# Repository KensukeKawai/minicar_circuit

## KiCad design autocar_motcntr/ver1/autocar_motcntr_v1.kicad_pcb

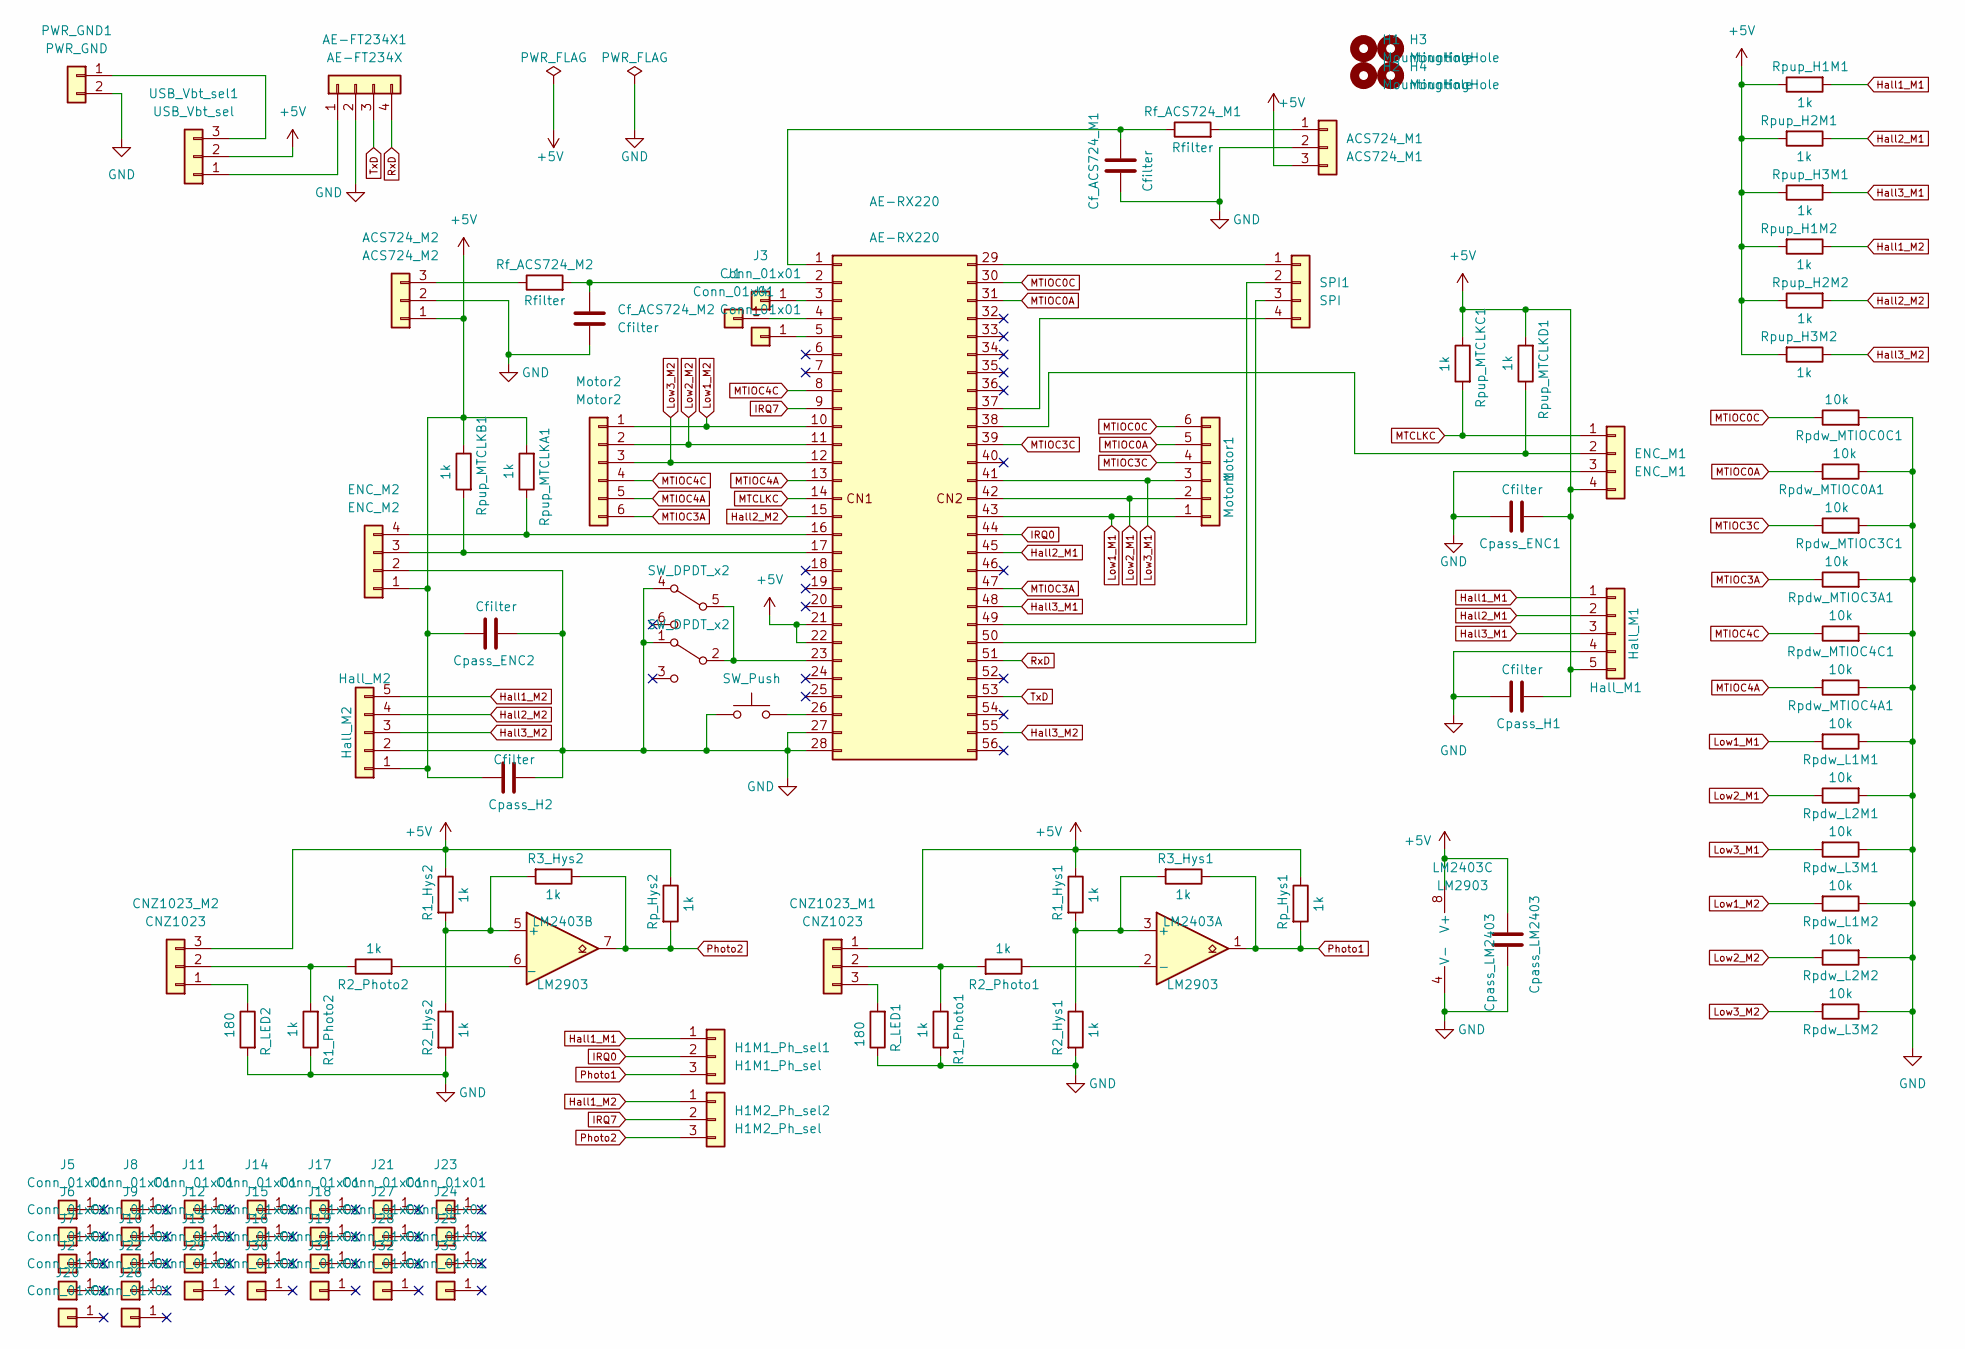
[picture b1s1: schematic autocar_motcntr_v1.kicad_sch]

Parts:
ACS724_M1: ACS724_M1; JST_XH_B3B-XH-A_1x03_P2.50mm_Vertical
ACS724_M2: ACS724_M2; JST_XH_B3B-XH-A_1x03_P2.50mm_Vertical
AE-FT234X1: AE-FT234X
AE-RX220: AE-RX220
CNZ1023_M1, CNZ1023_M2: CNZ1023; JST_XH_B3B-XH-A_1x03_P2.50mm_Vertical
Cf_ACS724_M1, Cf_ACS724_M2: Cfilter; C_Disc_D3.0mm_W2.0mm_P2.50mm
Cpass_ENC1, Cpass_ENC2: Cfilter; C_Disc_D3.0mm_W2.0mm_P2.50mm
Cpass_H1, Cpass_H2: Cfilter; C_Disc_D3.0mm_W2.0mm_P2.50mm
Cpass_LM2403: Cpass_LM2403; C_Disc_D3.0mm_W2.0mm_P2.50mm
ENC_M1: ENC_M1; JST_XH_B4B-XH-A_1x04_P2.50mm_Vertical
ENC_M2: ENC_M2; JST_XH_B4B-XH-A_1x04_P2.50mm_Vertical
H1, H2, H3, H4: MountingHole; MountingHole_3.2mm_M3
H1M1_Ph_sel1: H1M1_Ph_sel; PinHeader_1x03_P2.54mm_Vertical
H1M2_Ph_sel2: H1M2_Ph_sel; PinHeader_1x03_P2.54mm_Vertical
Hall_M1: Hall_M1; JST_XH_B5B-XH-A_1x05_P2.50mm_Vertical
Hall_M2: Hall_M2; JST_XH_B5B-XH-A_1x05_P2.50mm_Vertical
J1, J2, J3, J4, J5, J6, J7, J8, J9, J10, J11, J12, J13, J14, J15, J16, J17, J18, J19, J20, J21, J22, J23, J24, J25, J26, J27, J28, J29, J30, J31, J32, J33: Conn_01x01; TestPoint_THTPad_D1.5mm_Drill0.7mm
LM2403: LM2903; DIP-8_W7.62mm
Motor1: Motor1; JST_XH_B6B-XH-A_1x06_P2.50mm_Vertical
Motor2: Motor2; JST_XH_B6B-XH-A_1x06_P2.50mm_Vertical
PWR_GND1: PWR_GND; TB-111-2
R1_Hys1, R1_Hys2, R1_Photo1, R1_Photo2, R2_Hys1, R2_Hys2, R2_Photo1, R2_Photo2: 1k; R_Axial_DIN0207_L6.3mm_D2.5mm_P2.54mm_Vertical
R3_Hys1, R3_Hys2: 1k; R_Axial_DIN0207_L6.3mm_D2.5mm_P7.62mm_Horizontal
R_LED1, R_LED2: 180; R_Axial_DIN0207_L6.3mm_D2.5mm_P2.54mm_Vertical
Rf_ACS724_M1, Rf_ACS724_M2: Rfilter; R_Axial_DIN0207_L6.3mm_D2.5mm_P2.54mm_Vertical
Rp_Hys1, Rp_Hys2: 1k; R_Axial_DIN0207_L6.3mm_D2.5mm_P2.54mm_Vertical
Rpdw_L1M1, Rpdw_L1M2, Rpdw_L2M1, Rpdw_L2M2, Rpdw_L3M1, Rpdw_L3M2: 10k; R_Axial_DIN0207_L6.3mm_D2.5mm_P2.54mm_Vertical
Rpdw_MTIOC0A1, Rpdw_MTIOC0C1, Rpdw_MTIOC3A1, Rpdw_MTIOC3C1, Rpdw_MTIOC4A1, Rpdw_MTIOC4C1: 10k; R_Axial_DIN0207_L6.3mm_D2.5mm_P2.54mm_Vertical
Rpup_H1M1, Rpup_H1M2, Rpup_H2M1, Rpup_H2M2, Rpup_H3M1, Rpup_H3M2: 1k; R_Axial_DIN0207_L6.3mm_D2.5mm_P2.54mm_Vertical
Rpup_MTCLKA1: 1k; R_Axial_DIN0207_L6.3mm_D2.5mm_P2.54mm_Vertical
Rpup_MTCLKB1: 1k; R_Axial_DIN0207_L6.3mm_D2.5mm_P2.54mm_Vertical
Rpup_MTCLKC1: 1k; R_Axial_DIN0207_L6.3mm_D2.5mm_P2.54mm_Vertical
Rpup_MTCLKD1: 1k; R_Axial_DIN0207_L6.3mm_D2.5mm_P2.54mm_Vertical
SPI1: SPI; JST_XH_B4B-XH-A_1x04_P2.50mm_Vertical
SW1: SW_DPDT_x2; SW_E-Switch_EG1271_DPDT
SW2: SW_Push; SW_Tactile_Straight_KSA0Axx1LFTR
USB_Vbt_sel1: USB_Vbt_sel; PinHeader_1x03_P2.54mm_Vertical

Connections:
+5V: ACS724_M1.3, ACS724_M2.1, AE-RX220.21 (CN1-21), AE-RX220.22 (CN1-22), CNZ1023_M1.1, CNZ1023_M2.3, Cpass_ENC1.2, Cpass_ENC2.1, Cpass_H1.2, Cpass_H2.1, Cpass_LM2403.2, ENC_M1.4, ENC_M2.1, Hall_M1.5, Hall_M2.1, LM2403.8 (V+), R1_Hys1.1, R1_Hys2.1, Rp_Hys1.1, Rp_Hys2.1, Rpup_H1M1.1, Rpup_H1M2.2, Rpup_H2M1.2, Rpup_H2M2.1, Rpup_H3M1.1, Rpup_H3M2.2, Rpup_MTCLKA1.2, Rpup_MTCLKB1.1, Rpup_MTCLKC1.1, Rpup_MTCLKD1.2, USB_Vbt_sel1.2
GND: ACS724_M1.2, ACS724_M2.2, AE-FT234X1.2 (GND), AE-RX220.27 (CN1-27), AE-RX220.28 (CN1-28), Cf_ACS724_M1.2, Cf_ACS724_M2.2, Cpass_ENC1.1, Cpass_ENC2.2, Cpass_H1.1, Cpass_H2.2, Cpass_LM2403.1, ENC_M1.3, ENC_M2.2, Hall_M1.4, Hall_M2.2, LM2403.4 (V-), PWR_GND1.2, R1_Photo1.2, R1_Photo2.1, R2_Hys1.2, R2_Hys2.2, R_LED1.1, R_LED2.2, Rpdw_L1M1.1, Rpdw_L1M2.1, Rpdw_L2M1.2, Rpdw_L2M2.2, Rpdw_L3M1.1, Rpdw_L3M2.1, Rpdw_MTIOC0A1.1, Rpdw_MTIOC0C1.2, Rpdw_MTIOC3A1.2, Rpdw_MTIOC3C1.2, Rpdw_MTIOC4A1.1, Rpdw_MTIOC4C1.2, SW1.1 (A), SW1.4 (A), SW2.2
Hall1_M1: H1M1_Ph_sel1.1, Hall_M1.1, Rpup_H1M1.2
Hall1_M2: H1M2_Ph_sel2.1, Hall_M2.5, Rpup_H1M2.1
Hall2_M1: AE-RX220.45 (CN2-17), Hall_M1.2, Rpup_H2M1.1
Hall2_M2: AE-RX220.15 (CN1-15), Hall_M2.4, Rpup_H2M2.2
Hall3_M1: AE-RX220.48 (CN2-20), Hall_M1.3, Rpup_H3M1.2
Hall3_M2: AE-RX220.55 (CN2-27), Hall_M2.3, Rpup_H3M2.1
IRQ0: AE-RX220.44 (CN2-16), H1M1_Ph_sel1.2
IRQ7: AE-RX220.9 (CN1-09), H1M2_Ph_sel2.2
Low1_M1: AE-RX220.43 (CN2-15), Motor1.1, Rpdw_L1M1.2
Low1_M2: AE-RX220.10 (CN1-10), Motor2.1, Rpdw_L1M2.2
Low2_M1: AE-RX220.42 (CN2-14), Motor1.2, Rpdw_L2M1.1
Low2_M2: AE-RX220.11 (CN1-11), Motor2.2, Rpdw_L2M2.1
Low3_M1: AE-RX220.41 (CN2-13), Motor1.3, Rpdw_L3M1.2
Low3_M2: AE-RX220.12 (CN1-12), Motor2.3, Rpdw_L3M2.2
MTCLKC: AE-RX220.14 (CN1-14), ENC_M1.1, Rpup_MTCLKC1.2
MTIOC0A: AE-RX220.31 (CN2-03), Motor1.5, Rpdw_MTIOC0A1.2
MTIOC0C: AE-RX220.30 (CN2-02), Motor1.6, Rpdw_MTIOC0C1.1
MTIOC3A: AE-RX220.47 (CN2-19), Motor2.6, Rpdw_MTIOC3A1.1
MTIOC3C: AE-RX220.39 (CN2-11), Motor1.4, Rpdw_MTIOC3C1.1
MTIOC4A: AE-RX220.13 (CN1-13), Motor2.5, Rpdw_MTIOC4A1.2
MTIOC4C: AE-RX220.8 (CN1-08), Motor2.4, Rpdw_MTIOC4C1.1
unnamed: ACS724_M1.1, Rf_ACS724_M1.2
unnamed: ACS724_M2.3, Rf_ACS724_M2.1
unnamed: AE-FT234X1.1 (5V(VUSB)), USB_Vbt_sel1.1
unnamed: AE-RX220.1 (CN1-01), Cf_ACS724_M1.1, Rf_ACS724_M1.1
unnamed: AE-RX220.2 (CN1-02), Cf_ACS724_M2.1, Rf_ACS724_M2.2
unnamed: AE-RX220.3 (CN1-03), J3.1
unnamed: AE-RX220.4 (CN1-04), J1.1
unnamed: AE-RX220.5 (CN1-05), J4.1
unnamed: AE-RX220.16 (CN1-16), ENC_M2.4, Rpup_MTCLKA1.1
unnamed: AE-RX220.17 (CN1-17), ENC_M2.3, Rpup_MTCLKB1.2
unnamed: AE-RX220.23 (CN1-23), SW1.2 (B), SW1.5 (B)
unnamed: AE-RX220.26 (CN1-26), SW2.1
unnamed: AE-RX220.29 (CN2-01), SPI1.1
unnamed: AE-RX220.37 (CN2-09), SPI1.4
unnamed: AE-RX220.38 (CN2-10), ENC_M1.2, Rpup_MTCLKD1.1
unnamed: AE-RX220.49 (CN2-21), SPI1.2
unnamed: AE-RX220.50 (CN2-22), SPI1.3
unnamed: CNZ1023_M1.2, R1_Photo1.1, R2_Photo1.2
unnamed: CNZ1023_M1.3, R_LED1.2
unnamed: CNZ1023_M2.1, R_LED2.1
unnamed: CNZ1023_M2.2, R1_Photo2.2, R2_Photo2.1
unnamed: LM2403.2 (-), R2_Photo1.1
unnamed: LM2403.3 (+), R1_Hys1.2, R2_Hys1.1, R3_Hys1.2
unnamed: LM2403.5 (+), R1_Hys2.2, R2_Hys2.1, R3_Hys2.2
unnamed: LM2403.6 (_), R2_Photo2.2
unnamed: PWR_GND1.1, USB_Vbt_sel1.3
Photo1: H1M1_Ph_sel1.3, LM2403.1, R3_Hys1.1, Rp_Hys1.2
Photo2: H1M2_Ph_sel2.3, LM2403.7, R3_Hys2.1, Rp_Hys2.2
RxD: AE-FT234X1.4 (RxD), AE-RX220.51 (CN2-23)
TxD: AE-FT234X1.3 (TxD), AE-RX220.53 (CN2-25)

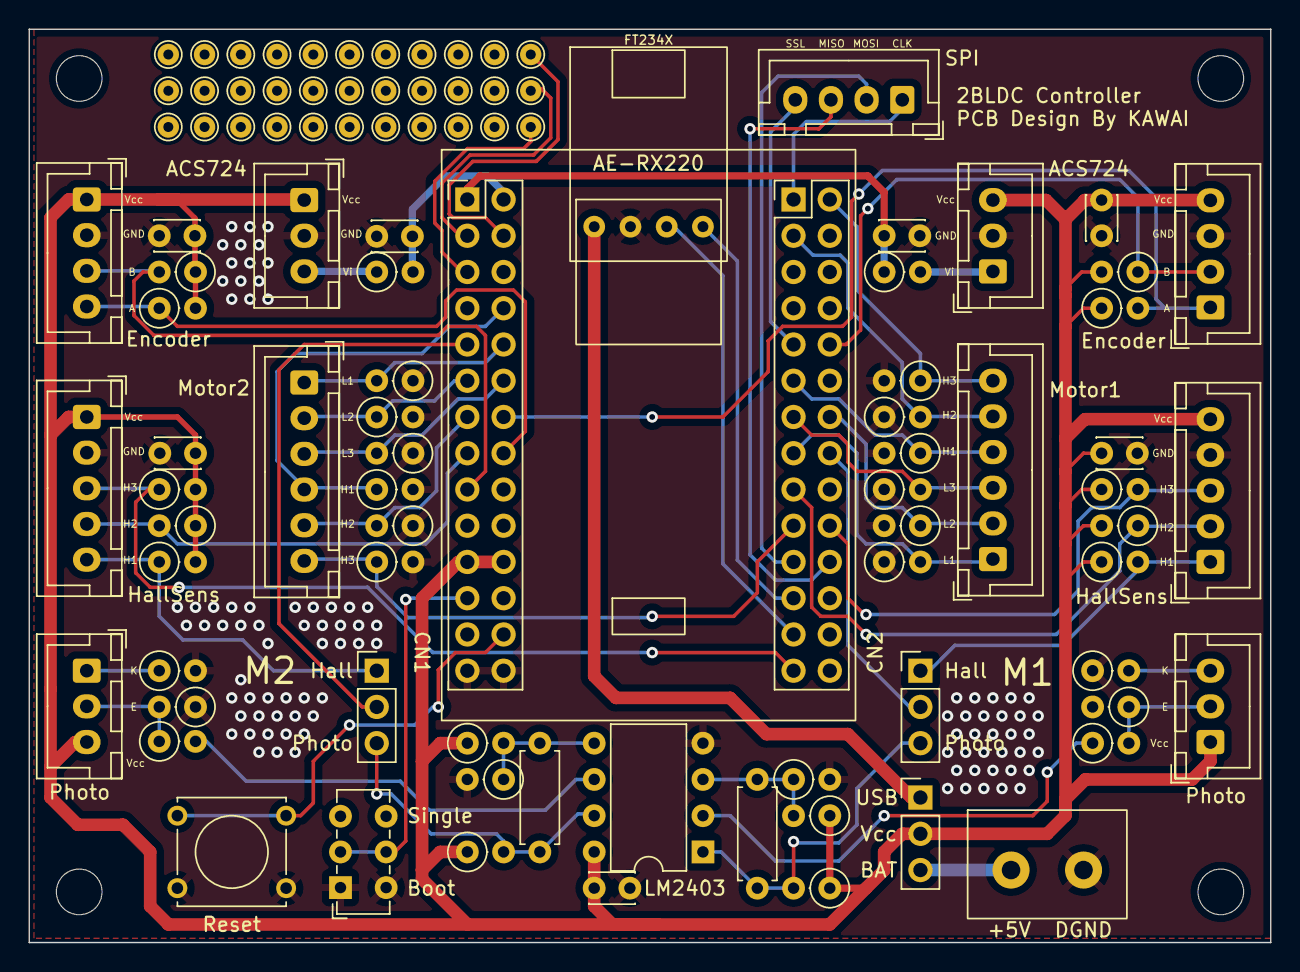
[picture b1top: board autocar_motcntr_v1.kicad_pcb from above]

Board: 2 copper layers, 87.0 x 64.0 mm, 102 parts (0 on the bottom side), 53 nets.

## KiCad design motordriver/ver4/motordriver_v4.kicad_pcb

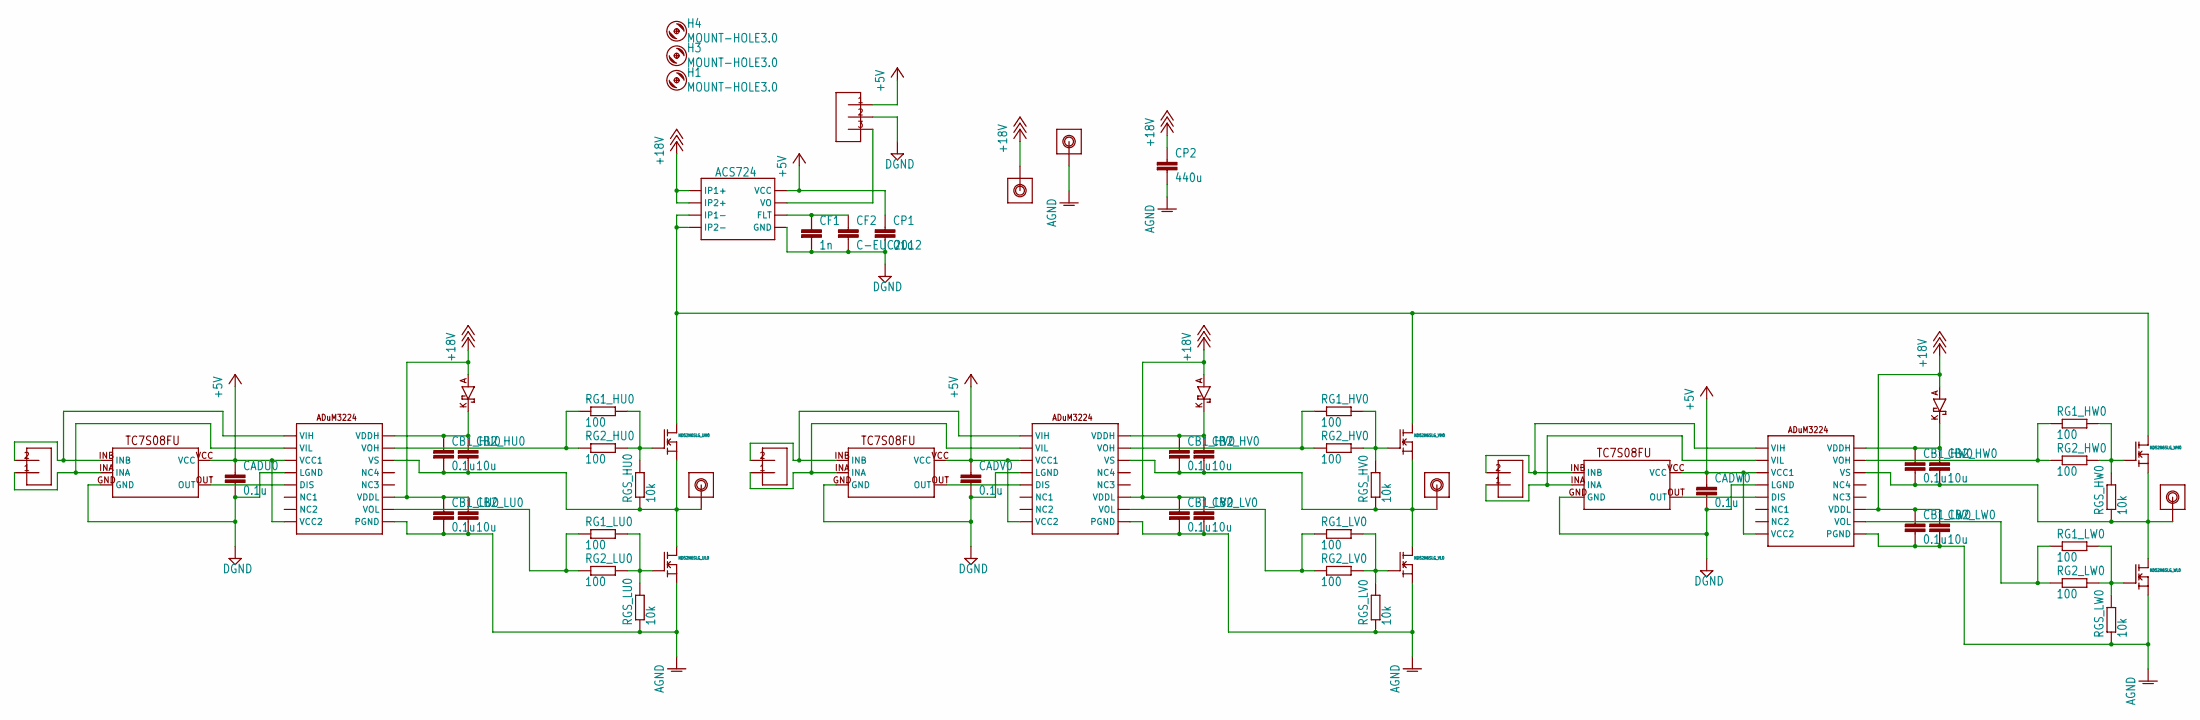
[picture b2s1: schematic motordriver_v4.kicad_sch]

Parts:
ACS724: ACS724
ADUM3224_U0, ADUM3224_V0: ADUM3224; SO16
CADU0: 0.1u; C2012
CADV0: 0.1u; C2012
CADW0: 0.1u; C2012
CB1_HU0, CB1_HV0, CB1_HW0, CB1_LU0, CB1_LV0, CB1_LW0: 0.1u; C2012
CB2_HU0, CB2_HV0, CB2_HW0, CB2_LU0, CB2_LV0, CB2_LW0: 10u; C3225
CF1: 1n; C1608
CF2: C-EUC2012; C2012
CP1: 01u; C2012
CP2: 440u; CP_Radial_D10.0mm_P5.00mm
H1, H3, H4: MOUNT-HOLE3.0; 3,0
ND52N6SLG_UH0, ND52N6SLG_UL0, ND52N6SLG_VH0, ND52N6SLG_VL0, ND52N6SLG_WH0, ND52N6SLG_WL0: ND52N6SLG; TO252
RG1_HU0, RG1_HV0, RG1_HW0, RG1_LU0, RG1_LV0, RG1_LW0, RG2_HU0, RG2_HV0, RG2_HW0, RG2_LU0, RG2_LV0, RG2_LW0: 100; R3216
RGS_HU0: 10k; R3216
RGS_HV0: 10k; R3216
RGS_HW0: 10k; R3216
RGS_LU0: 10k; R3216
RGS_LV0: 10k; R3216
RGS_LW0: 10k; R3216
SBD_U0: SBR1U200P1
SBD_V0: SBR1U200P1
U$1, U$7, U$14, U$15, U$16: PV-3
U$2, U$9, U$13: B2B-XH-A
U$4: B3B-XH-A
U$5, U$8, U$12: TC7S08FU
U$10: ADUM3224; SO16
U$11: SBR1U200P1

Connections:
+5V: ACS724.VCC, ADUM3224_U0.VCC1, ADUM3224_U0.VCC2, ADUM3224_V0.VCC1, ADUM3224_V0.VCC2, CADU0.1, CADV0.1, CADW0.1, CP1.1, U$4.1, U$5.VCC, U$8.VCC, U$10.VCC1, U$10.VCC2, U$12.VCC
AGND: ADUM3224_U0.PGND, ADUM3224_V0.PGND, CB1_LU0.2, CB1_LV0.2, CB1_LW0.2, CB2_LU0.2, CB2_LV0.2, CB2_LW0.2, CP2.2, ND52N6SLG_UL0.3 (S), ND52N6SLG_VL0.3 (S), ND52N6SLG_WL0.3 (S), RGS_LU0.1, RGS_LV0.1, RGS_LW0.1, U$7.P$1, U$10.PGND; also elsewhere on the board
DGND: ACS724.GND, ADUM3224_U0.LGND, ADUM3224_V0.LGND, CADU0.2, CADV0.2, CADW0.2, CF1.2, CF2.2, CP1.2, U$4.2, U$5.GND, U$8.GND, U$10.LGND, U$12.GND
unnamed: ACS724.IP1-, ACS724.IP2-, ND52N6SLG_UH0.4 (D), ND52N6SLG_VH0.4 (D), ND52N6SLG_WH0.4 (D)
unnamed: ACS724.FLT, CF1.1, CF2.1
unnamed: ADUM3224_U0.VOH, RG1_HU0.1, RG2_HU0.1
unnamed: ADUM3224_U0.DIS, U$5.OUT
unnamed: ND52N6SLG_UL0.1 (G), RG1_LU0.2, RG2_LU0.2, RGS_LU0.2
unnamed: ADUM3224_U0.VIH, U$2.2, U$5.INB
unnamed: ND52N6SLG_UH0.1 (G), RG1_HU0.2, RG2_HU0.2, RGS_HU0.2
unnamed: ADUM3224_U0.VOL, RG1_LU0.1, RG2_LU0.1
unnamed: ND52N6SLG_VL0.1 (G), RG1_LV0.2, RG2_LV0.2, RGS_LV0.2
unnamed: ADUM3224_U0.VDDH, CB1_HU0.1, CB2_HU0.1, SBD_U0.K
unnamed: ADUM3224_U0.VS, CB1_HU0.2, CB2_HU0.2, ND52N6SLG_UH0.3 (S), ND52N6SLG_UL0.4 (D), RGS_HU0.1, U$14.P$1
unnamed: ADUM3224_U0.VIL, U$2.1, U$5.INA
unnamed: ND52N6SLG_VH0.1 (G), RG1_HV0.2, RG2_HV0.2, RGS_HV0.2
unnamed: ADUM3224_V0.VDDH, CB1_HV0.1, CB2_HV0.1, SBD_V0.K
unnamed: ADUM3224_V0.VS, CB1_HV0.2, CB2_HV0.2, ND52N6SLG_VH0.3 (S), ND52N6SLG_VL0.4 (D), RGS_HV0.1, U$15.P$1
unnamed: ADUM3224_V0.VOH, RG1_HV0.1, RG2_HV0.1
unnamed: ADUM3224_V0.VOL, RG1_LV0.1, RG2_LV0.1
unnamed: ADUM3224_V0.DIS, U$8.OUT
unnamed: ADUM3224_V0.VIH, U$8.INB, U$9.2
unnamed: ADUM3224_V0.VIL, U$8.INA, U$9.1
unnamed: ACS724.VO, U$4.3
unnamed: ND52N6SLG_WL0.1 (G), RG1_LW0.2, RG2_LW0.2, RGS_LW0.2
unnamed: ND52N6SLG_WH0.1 (G), RG1_HW0.2, RG2_HW0.2, RGS_HW0.2
unnamed: CB1_HW0.1, CB2_HW0.1, U$10.VDDH, U$11.K
unnamed: CB1_HW0.2, CB2_HW0.2, ND52N6SLG_WH0.3 (S), ND52N6SLG_WL0.4 (D), RGS_HW0.1, U$10.VS, U$16.P$1
unnamed: RG1_HW0.1, RG2_HW0.1, U$10.VOH
unnamed: RG1_LW0.1, RG2_LW0.1, U$10.VOL
unnamed: U$10.DIS, U$12.OUT
unnamed: U$10.VIH, U$12.INB, U$13.2
unnamed: U$10.VIL, U$12.INA, U$13.1

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
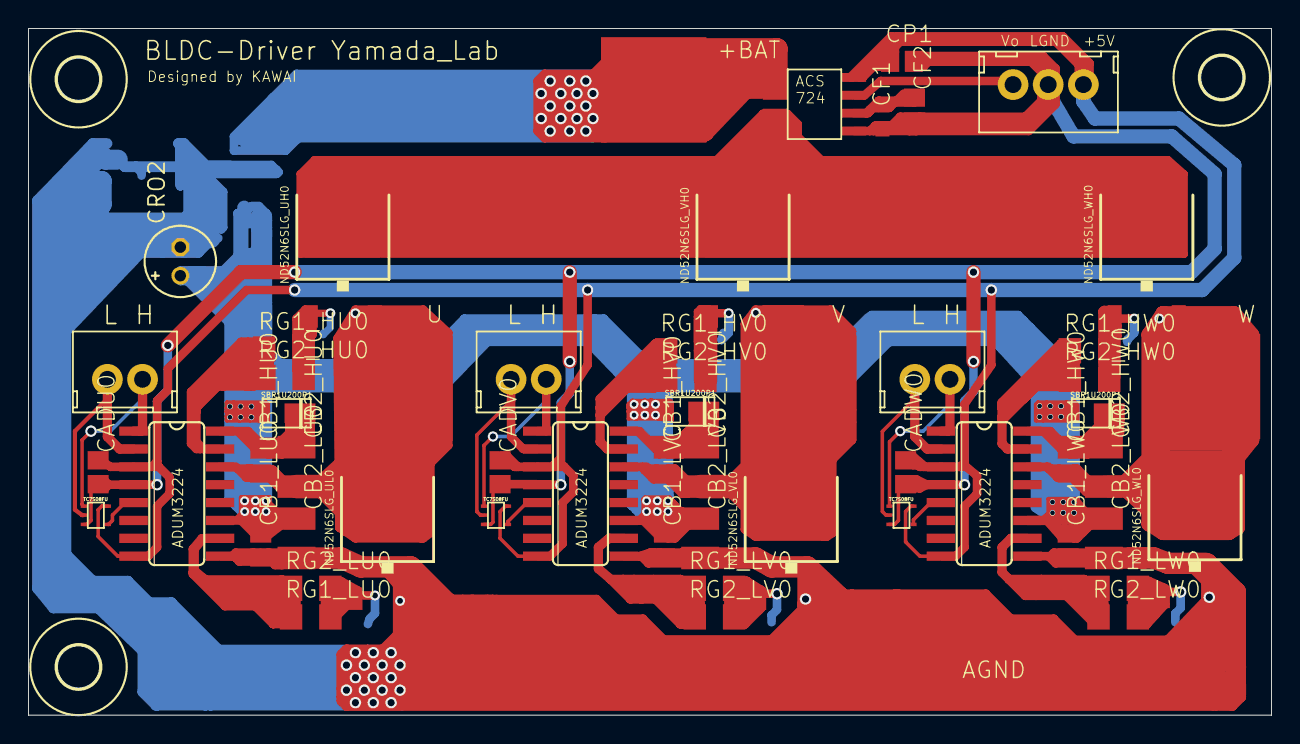
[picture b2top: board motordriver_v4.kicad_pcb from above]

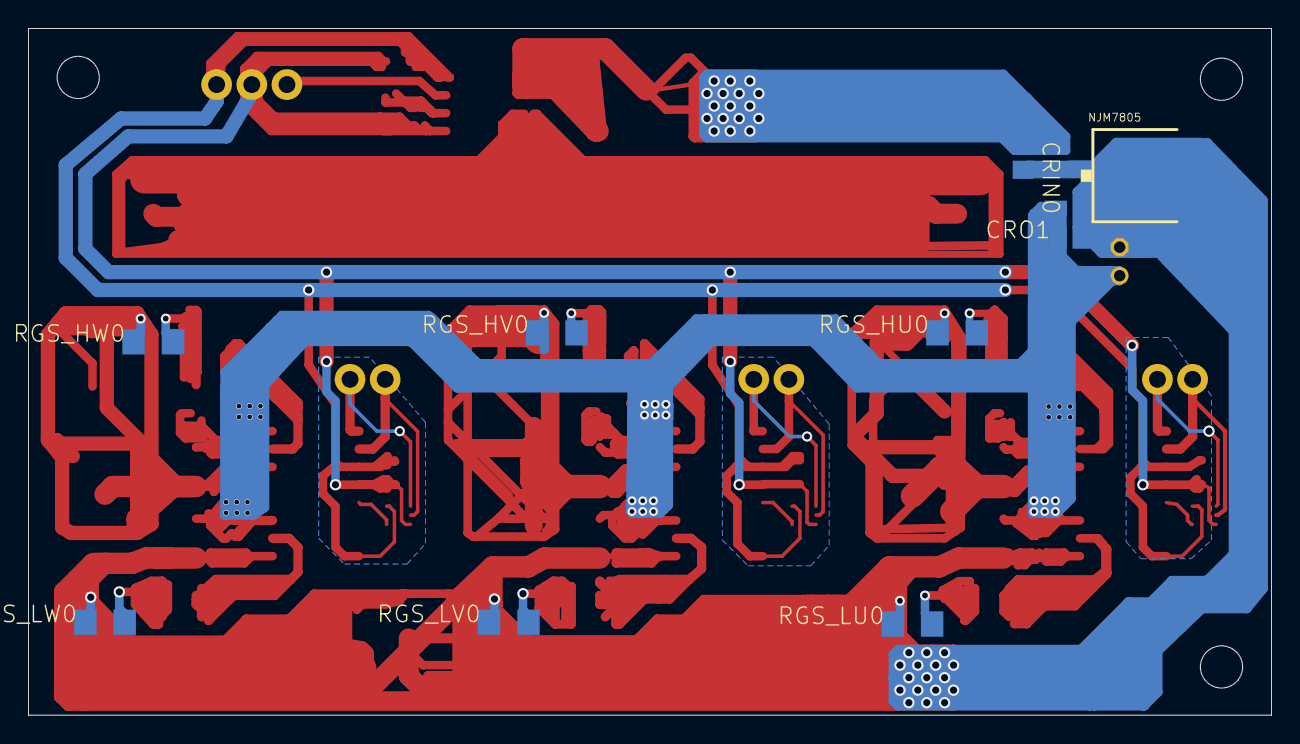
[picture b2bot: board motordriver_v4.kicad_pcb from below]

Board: 2 copper layers, 88.4 x 48.8 mm, 68 parts (9 on the bottom side), 35 nets.

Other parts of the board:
CRIN0: 1u; C2012
CRO1: 0.1u; C2012
CRO2: 47u; E2-5
NJM7805: NJM7805SDL1; TO252

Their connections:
AGND: CRIN0.2, CRO1.2, CRO2.-, NJM7805.2; also elsewhere on the board

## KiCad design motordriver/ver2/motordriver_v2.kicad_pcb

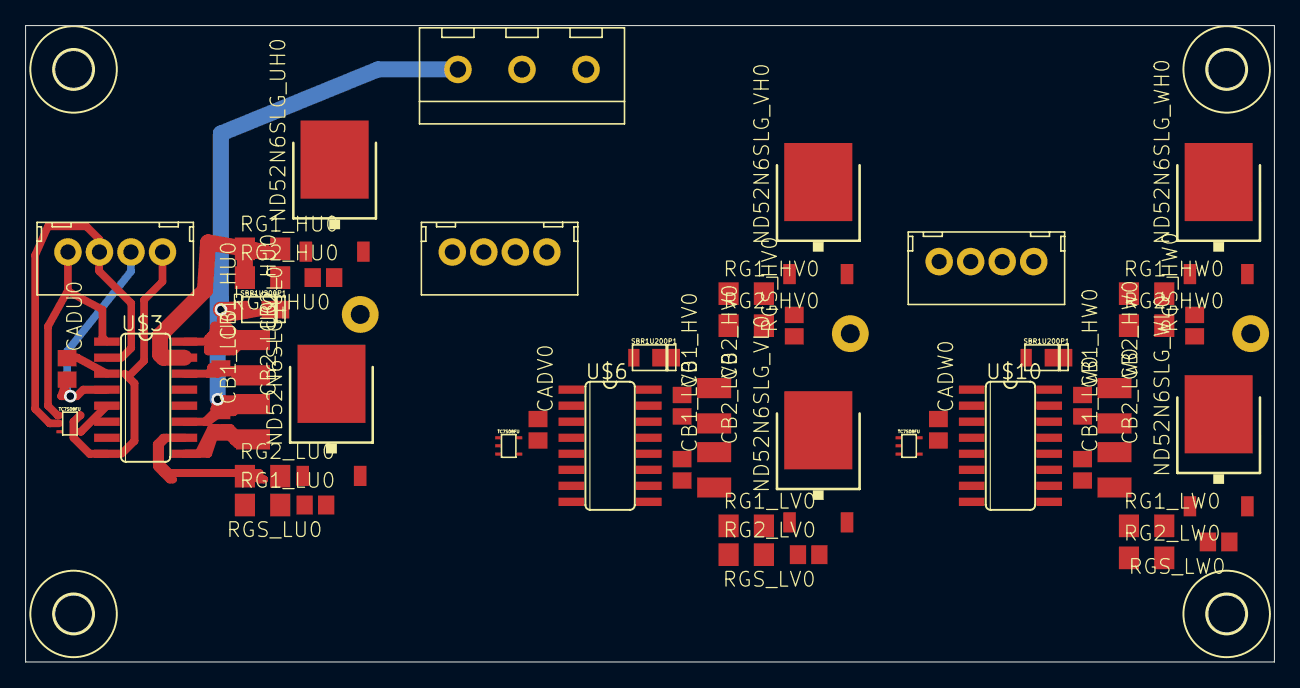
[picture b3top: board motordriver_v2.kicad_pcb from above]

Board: 2 copper layers, 99.0 x 50.5 mm, 59 parts (0 on the bottom side), 36 nets.

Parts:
CADU0: 0.1u; C2012
CADV0: 0.1u; C2012
CADW0: 0.1u; C2012
CB1_HU0, CB1_HV0, CB1_HW0, CB1_LU0, CB1_LV0, CB1_LW0: 0.1u; C2012
CB2_HU0, CB2_HV0, CB2_HW0, CB2_LU0, CB2_LV0, CB2_LW0: 10u; C3225
H1, H2, H3, H4: MOUNT-HOLE3.0; 3,0
ND52N6SLG_UH0, ND52N6SLG_UL0, ND52N6SLG_VH0, ND52N6SLG_VL0, ND52N6SLG_WH0, ND52N6SLG_WL0: ND52N6SLG; TO252
RG1_HU0, RG1_HV0, RG1_HW0, RG1_LU0, RG1_LV0, RG1_LW0, RG2_HU0, RG2_HV0, RG2_HW0, RG2_LU0, RG2_LV0, RG2_LW0: 100; R3216
RGS_HU0: 10k; R2012
RGS_HV0: 10k; R2012
RGS_HW0: 10k; R2012
RGS_LU0: 10k; R2012
RGS_LV0: 10k; R2012
RGS_LW0: 10k; R2012
SBD_U0: SBR1U200P1
SBD_V0: SBR1U200P1
U0, U1, U2: TH_HOLE_1.5MM
U$1, U$2, U$4: B4B-XH-A
U$3, U$6, U$10: ADUM3224; SO16
U$5, U$8, U$12: TC7S08FU
U$7: TERMINAL_3PIN
U$11: SBR1U200P1

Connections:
+5V: CADW0.1, U$4.1, U$10.VCC1, U$10.VCC2, U$12.VCC
+18V: ND52N6SLG_UH0.4, ND52N6SLG_VH0.4, ND52N6SLG_WH0.4, U$7.2
AGND: CB1_LU0.2, CB1_LV0.2, CB1_LW0.2, CB2_LU0.2, CB2_LV0.2, CB2_LW0.2, ND52N6SLG_UL0.3, ND52N6SLG_VL0.3, ND52N6SLG_WL0.3, RGS_LU0.1, RGS_LV0.1, RGS_LW0.1, U$3.PGND, U$6.PGND, U$7.1, U$10.PGND
unnamed: CADV0.1, U$2.1, U$6.VCC1, U$6.VCC2, U$8.VCC
unnamed: CADU0.1, U$1.1, U$3.VCC1, U$3.VCC2, U$5.VCC
unnamed: RG1_HU0.1, RG2_HU0.1, U$3.VOH
unnamed: U$3.DIS, U$5.OUT
unnamed: ND52N6SLG_UL0.1, RG1_LU0.2, RG2_LU0.2, RGS_LU0.2
unnamed: U$1.4, U$3.VIH, U$5.INB
unnamed: ND52N6SLG_UH0.1, RG1_HU0.2, RG2_HU0.2, RGS_HU0.2
unnamed: RG1_LU0.1, RG2_LU0.1, U$3.VOL
unnamed: CADV0.2, U$2.2, U$6.LGND, U$8.GND
unnamed: ND52N6SLG_VL0.1, RG1_LV0.2, RG2_LV0.2, RGS_LV0.2
unnamed: CB1_HU0.1, CB2_HU0.1, SBD_U0.K, U$3.VDDH
unnamed: CB1_HU0.2, CB2_HU0.2, ND52N6SLG_UH0.3, ND52N6SLG_UL0.4, RGS_HU0.1, U0.P$1, U$3.VS
unnamed: U$1.3, U$3.VIL, U$5.INA
unnamed: ND52N6SLG_VH0.1, RG1_HV0.2, RG2_HV0.2, RGS_HV0.2
unnamed: CB1_HV0.1, CB2_HV0.1, SBD_V0.K, U$6.VDDH
unnamed: CB1_HV0.2, CB2_HV0.2, ND52N6SLG_VH0.3, ND52N6SLG_VL0.4, RGS_HV0.1, U1.P$1, U$6.VS
unnamed: RG1_HV0.1, RG2_HV0.1, U$6.VOH
unnamed: RG1_LV0.1, RG2_LV0.1, U$6.VOL
unnamed: U$6.DIS, U$8.OUT
unnamed: U$2.4, U$6.VIH, U$8.INB
unnamed: U$2.3, U$6.VIL, U$8.INA
unnamed: CADW0.2, U$4.2, U$10.LGND, U$12.GND
unnamed: ND52N6SLG_WL0.1, RG1_LW0.2, RG2_LW0.2, RGS_LW0.2
unnamed: ND52N6SLG_WH0.1, RG1_HW0.2, RG2_HW0.2, RGS_HW0.2
unnamed: CB1_HW0.1, CB2_HW0.1, U$10.VDDH, U$11.K
unnamed: CB1_HW0.2, CB2_HW0.2, ND52N6SLG_WH0.3, ND52N6SLG_WL0.4, RGS_HW0.1, U2.P$1, U$10.VS
unnamed: RG1_HW0.1, RG2_HW0.1, U$10.VOH
unnamed: RG1_LW0.1, RG2_LW0.1, U$10.VOL
unnamed: U$10.DIS, U$12.OUT
unnamed: U$4.3, U$10.VIH, U$12.INB
unnamed: U$4.4, U$10.VIL, U$12.INA
unnamed: CADU0.2, U$1.2, U$3.LGND, U$5.GND
VCC: CB1_LU0.1, CB1_LV0.1, CB1_LW0.1, CB2_LU0.1, CB2_LV0.1, CB2_LW0.1, SBD_U0.A, SBD_V0.A, U$3.VDDL, U$6.VDDL, U$7.3, U$10.VDDL, U$11.A

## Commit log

2023-07-14 minicar circuit push
